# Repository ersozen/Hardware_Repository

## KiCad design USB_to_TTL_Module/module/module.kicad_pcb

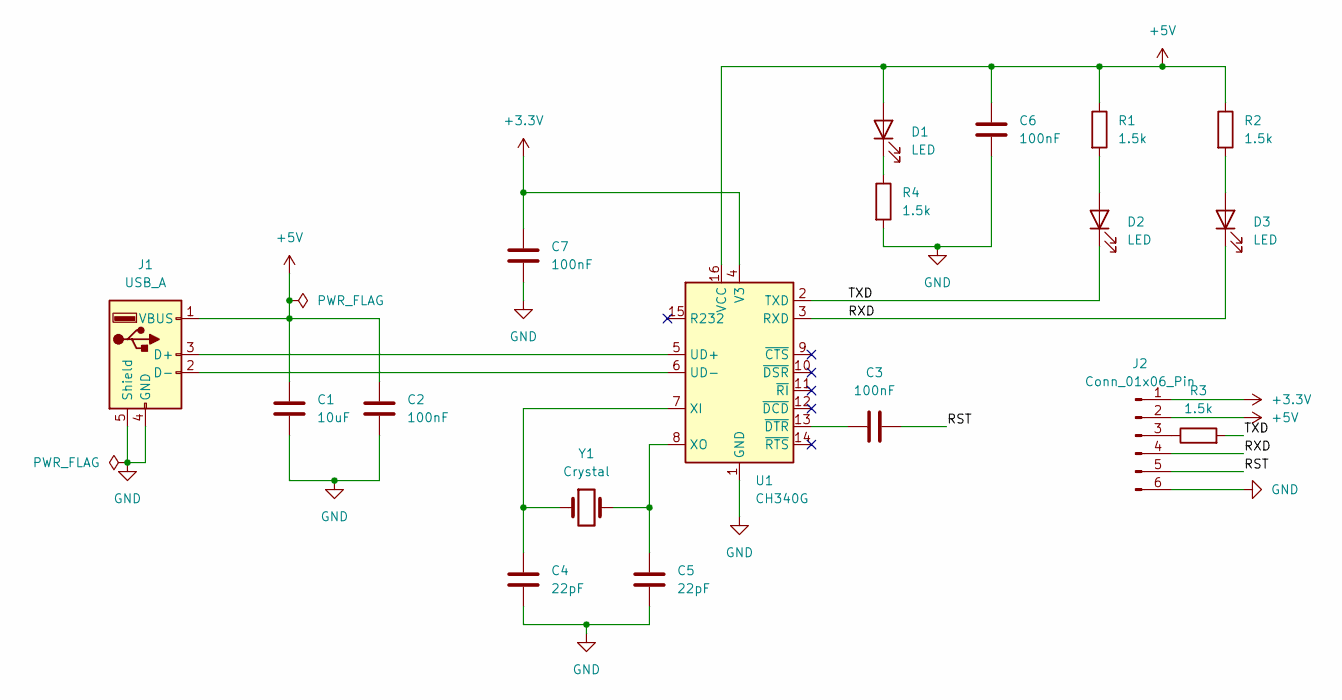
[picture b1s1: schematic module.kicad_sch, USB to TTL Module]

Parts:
C1: 10uF; C_0201_0603Metric
C2, C3, C6, C7: 100nF; C_0201_0603Metric
C4, C5: 22pF; C_0201_0603Metric
D1, D2, D3: LED; LED_0201_0603Metric
J1: USB_A; USB_A_CNCTech_1001-011-01101_Horizontal
J2: Conn_01x06_Pin; PinHeader_1x06_P2.54mm_Horizontal
R1, R2, R3, R4: 1.5k; R_0201_0603Metric
U1: CH340G; SOIC-16_3.9x9.9mm_P1.27mm
Y1: Crystal; Crystal_HC49-4H_Vertical

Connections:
+3.3V: C7.1, J2.1, U1.4 (V3)
+5V: C1.1, C2.1, C6.1, D1.2 (A), J1.1 (VBUS), J2.2, R1.1, R2.1, U1.16 (VCC)
/RST: C3.2, J2.5
/RXD: D3.1 (K), J2.4, U1.3 (RXD)
/TXD: D2.1 (K), R3.2, U1.2 (TXD)
GND: C1.2, C2.2, C4.2, C5.2, C6.2, C7.2, J1.4 (GND), J1.5 (Shield), J2.6, R4.2, U1.1 (GND)
unnamed: D1.1 (K), R4.1
unnamed: D2.2 (A), R1.2
unnamed: D3.2 (A), R2.2
unnamed: J1.3 (D+), U1.5 (UD+)
unnamed: J1.2 (D-), U1.6 (UD-)
unnamed: J2.3, R3.1
unnamed: C4.1, U1.7 (XI), Y1.1
unnamed: C5.1, U1.8 (XO), Y1.2
unnamed: C3.1, U1.13 (~DTR)

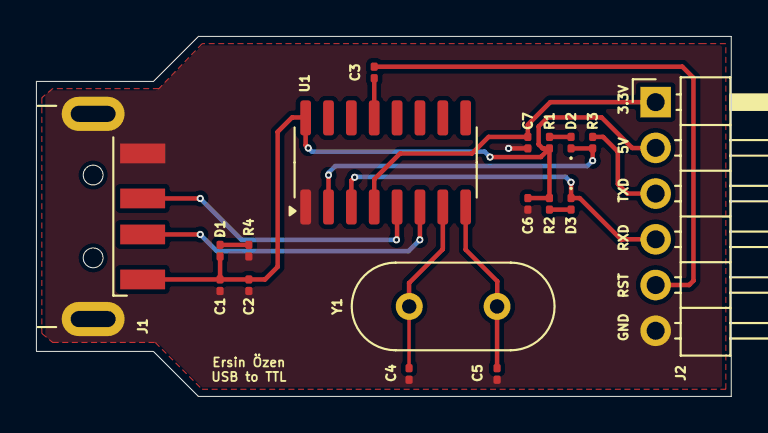
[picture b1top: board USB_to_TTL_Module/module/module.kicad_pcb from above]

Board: 2 copper layers, 38.6 x 20.0 mm, 18 parts (0 on the bottom side), 15 nets.

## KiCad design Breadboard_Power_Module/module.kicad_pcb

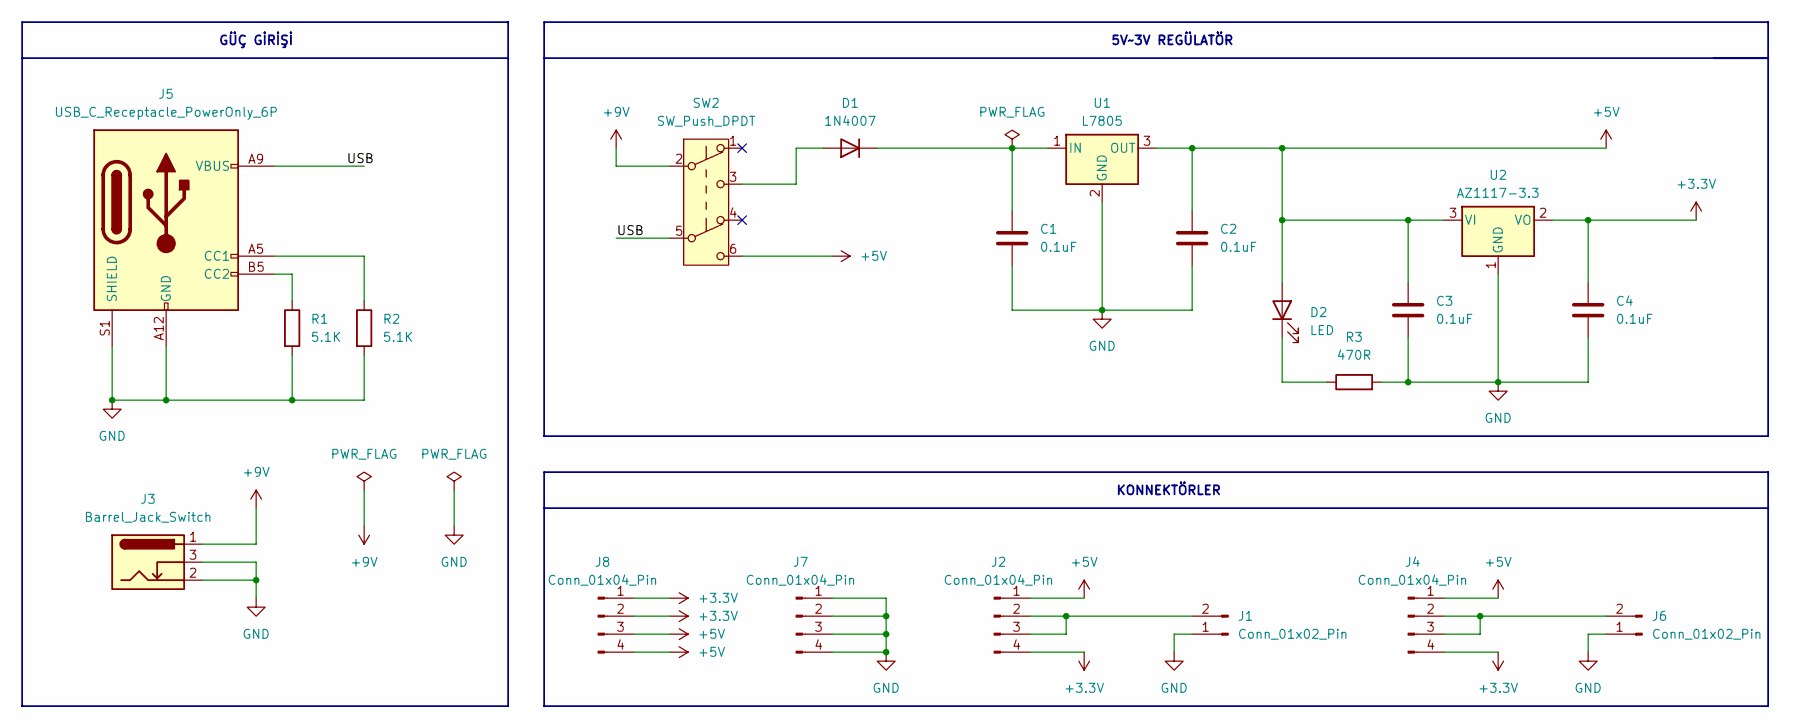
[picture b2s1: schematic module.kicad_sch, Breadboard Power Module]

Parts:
C1, C2, C3, C4: 0.1uF; C_Radial_D5.0mm_H11.0mm_P2.00mm
D1: 1N4007; D_DO-41_SOD81_P5.08mm_Vertical_AnodeUp
D2: LED; LED_D5.0mm
J1, J6: Conn_01x02_Pin; PinHeader_1x02_P2.54mm_Vertical
J2, J4, J7, J8: Conn_01x04_Pin; PinHeader_1x04_P2.54mm_Vertical
J3: Barrel_Jack_Switch; BarrelJack_Horizontal
J5: USB_C_Receptacle_PowerOnly_6P; USB_C_Receptacle_GCT_USB4125-xx-x-0190_6P_TopMnt_Horizontal
R1, R2: 5.1K; R_Axial_DIN0204_L3.6mm_D1.6mm_P5.08mm_Horizontal
R3: 470R; R_Axial_DIN0204_L3.6mm_D1.6mm_P5.08mm_Horizontal
SW2: SW_Push_DPDT; SW_CK_JS202011AQN_DPDT_Angled
U1: L7805; TO-220-3_Vertical
U2: AZ1117-3.3; TO-220-3_Vertical

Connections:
+3.3V: C4.1, J2.4, J4.4, J8.1, J8.2, U2.2 (VO)
+5V: C2.1, C3.1, D2.2 (A), J2.1, J4.1, J8.3, J8.4, SW2.6 (C), U1.3 (OUT), U2.3 (VI)
+9V: J3.1, SW2.2 (B)
/USB: J5.A9 (VBUS), J5.B9 (VBUS), SW2.5 (B)
GND: C1.2, C2.2, C3.2, C4.2, J1.1, J3.2, J3.3, J5.A12 (GND), J5.B12 (GND), J5.S1 (SHIELD), J6.1, J7.1, J7.2, J7.3, J7.4, R1.2, R2.2, R3.2, U1.2 (GND), U2.1 (GND)
unnamed: D1.2 (A), SW2.3 (C)
unnamed: C1.1, D1.1 (K), U1.1 (IN)
unnamed: D2.1 (K), R3.1
unnamed: J1.2, J2.2, J2.3
unnamed: J4.2, J4.3, J6.2
unnamed: J5.A5 (CC1), R2.1
unnamed: J5.B5 (CC2), R1.1

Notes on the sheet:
5V~3V REGÜLATÖR
GÜÇ GİRİŞİ
KONNEKTÖRLER

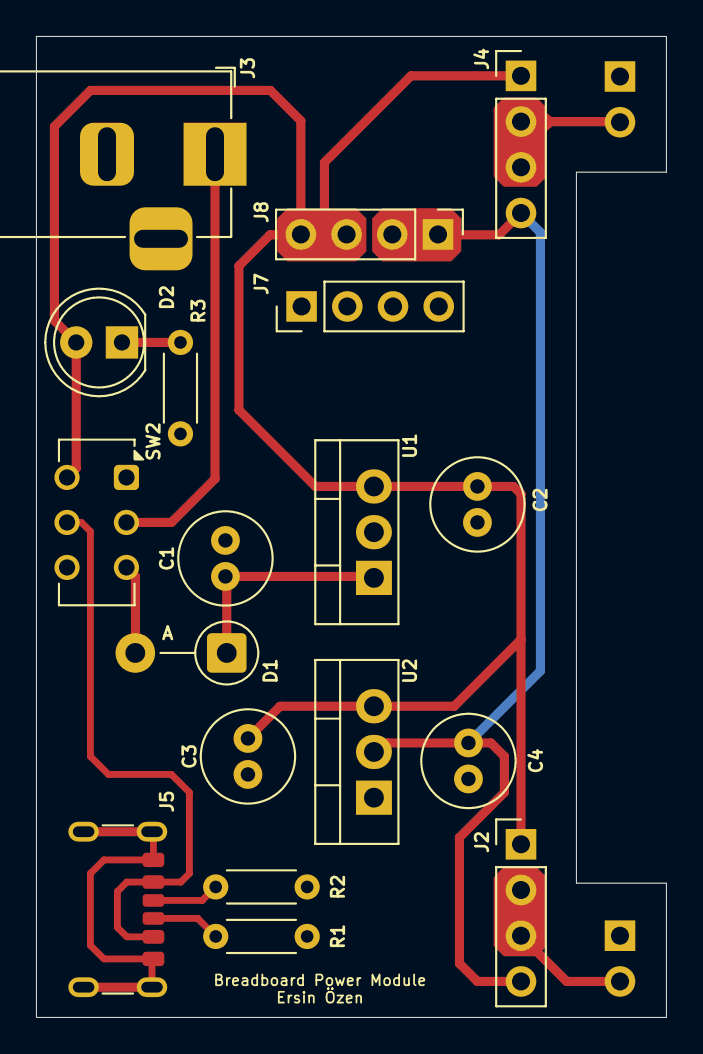
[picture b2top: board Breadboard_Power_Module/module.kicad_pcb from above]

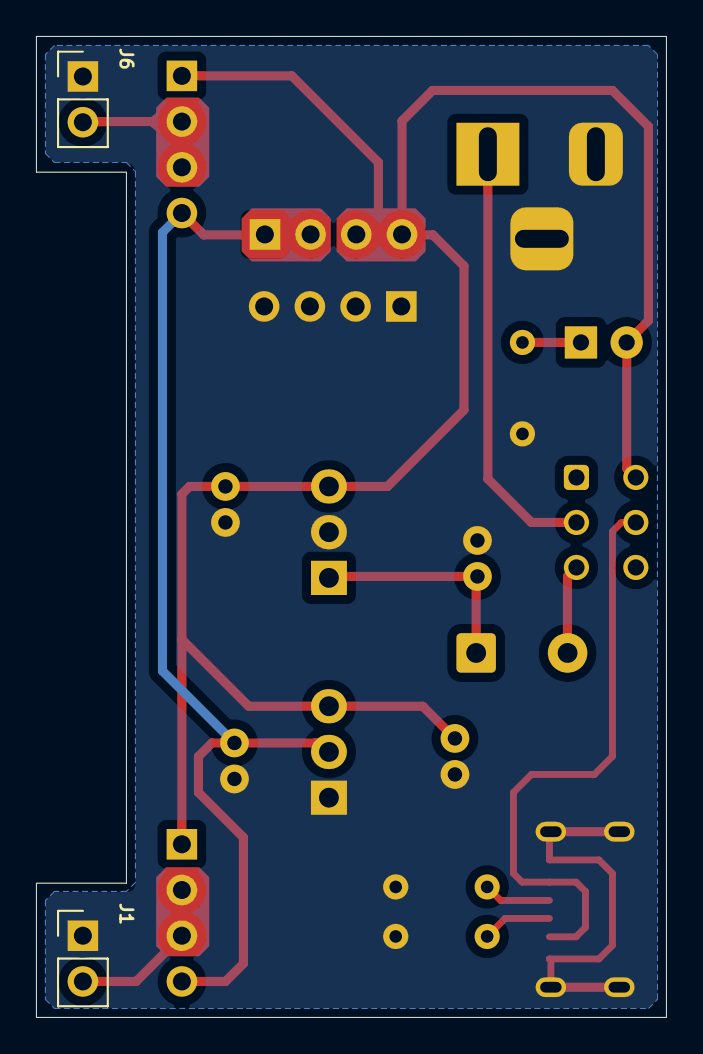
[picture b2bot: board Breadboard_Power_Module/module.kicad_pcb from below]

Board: 2 copper layers, 35.0 x 54.5 mm, 20 parts (2 on the bottom side), 12 nets.
